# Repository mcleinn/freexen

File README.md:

Building blocks for a DIY 56*x key velocity-sensitive microtonal keyboard

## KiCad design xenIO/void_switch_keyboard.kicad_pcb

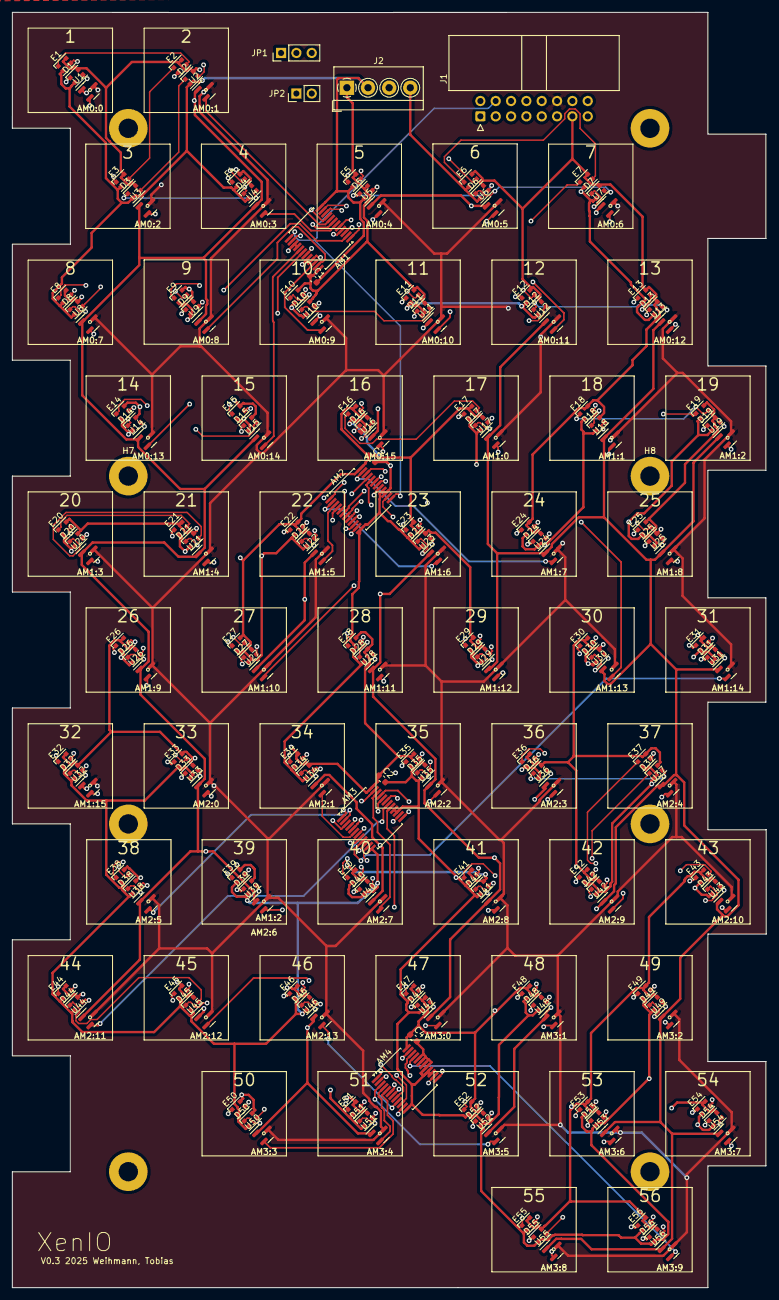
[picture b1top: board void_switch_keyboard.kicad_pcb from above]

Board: 4 copper layers, 124.8 x 211.2 mm, 244 parts (0 on the bottom side), 183 nets.

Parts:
AM0:0: 1; VoidSwitch_1u_SMD
AM0:1: 2; VoidSwitch_1u_SMD
AM0:2: 3; VoidSwitch_1u_SMD
AM0:3: 4; VoidSwitch_1u_SMD
AM0:4: 5; VoidSwitch_1u_SMD
AM0:5: 6; VoidSwitch_1u_SMD
AM0:6: 7; VoidSwitch_1u_SMD
AM0:7: 8; VoidSwitch_1u_SMD
AM0:8: 9; VoidSwitch_1u_SMD
AM0:9: 10; VoidSwitch_1u_SMD
AM0:10: 11; VoidSwitch_1u_SMD
AM0:11: 12; VoidSwitch_1u_SMD
AM0:12: 13; VoidSwitch_1u_SMD
AM0:13: 14; VoidSwitch_1u_SMD
AM0:14: 15; VoidSwitch_1u_SMD
AM0:15: 16; VoidSwitch_1u_SMD
AM1, AM2, AM3, AM4: CD74HC4067SM; SSOP-24_5.3x8.2mm_P0.65mm
AM1:0: 17; VoidSwitch_1u_SMD
AM1:1: 18; VoidSwitch_1u_SMD
AM1:2: 19; VoidSwitch_1u_SMD
AM1:3: 20; VoidSwitch_1u_SMD
AM1:4: 21; VoidSwitch_1u_SMD
AM1:5: 22; VoidSwitch_1u_SMD
AM1:6: 23; VoidSwitch_1u_SMD
AM1:7: 24; VoidSwitch_1u_SMD
AM1:8: 25; VoidSwitch_1u_SMD
AM1:9: 26; VoidSwitch_1u_SMD
AM1:10: 27; VoidSwitch_1u_SMD
AM1:11: 28; VoidSwitch_1u_SMD
AM1:12: 29; VoidSwitch_1u_SMD
AM1:13: 30; VoidSwitch_1u_SMD
AM1:14: 31; VoidSwitch_1u_SMD
AM1:15: 32; VoidSwitch_1u_SMD
AM2:0: 33; VoidSwitch_1u_SMD
AM2:1: 34; VoidSwitch_1u_SMD
AM2:2: 35; VoidSwitch_1u_SMD
AM2:3: 36; VoidSwitch_1u_SMD
AM2:4: 37; VoidSwitch_1u_SMD
AM2:5: 38; VoidSwitch_1u_SMD
AM2:6: 39; VoidSwitch_1u_SMD
AM2:7: 40; VoidSwitch_1u_SMD
AM2:8: 41; VoidSwitch_1u_SMD
AM2:9: 42; VoidSwitch_1u_SMD
AM2:10: 43; VoidSwitch_1u_SMD
AM2:11: 44; VoidSwitch_1u_SMD
AM2:12: 45; VoidSwitch_1u_SMD
AM2:13: 46; VoidSwitch_1u_SMD
AM3:0: 47; VoidSwitch_1u_SMD
AM3:1: 48; VoidSwitch_1u_SMD
AM3:2: 49; VoidSwitch_1u_SMD
AM3:3: 50; VoidSwitch_1u_SMD
AM3:4: 51; VoidSwitch_1u_SMD
AM3:5: 52; VoidSwitch_1u_SMD
AM3:6: 53; VoidSwitch_1u_SMD
AM3:7: 54; VoidSwitch_1u_SMD
AM3:8: 55; VoidSwitch_1u_SMD
AM3:9: 56; VoidSwitch_1u_SMD
C1, C2, C3, C4: 0.1uF; C_0603_1608Metric
D1, D2, D3, D4, D5, D6, D7, D8, D9, D10, D11, D12, D13, D14, D15, D16, D17, D18, D19, D20, D21, D22, D23, D24, D25, D26, D27, D28, D29, D30, D31, D32, D33, D34, D35, D36, D37, D38, D39, D40, D41, D42, D43, D44, D45, D46, D47, D48, D49, D50, D51, D52, D53, D54, D55, D56: WS2812B-2020; LED_WS2812B-2020_PLCC4_2.0x2.0mm
E1, E2, E3, E4, E5, E6, E7, E8, E9, E10, E11, E12, E13, E14, E15, E16, E17, E18, E19, E20, E21, E22, E23, E24, E25, E26, E27, E28, E29, E30, E31, E32, E33, E34, E35, E36, E37, E38, E39, E40, E41, E42, E43, E44, E45, E46, E47, E48, E49, E50, E51, E52, E53, E54, E55, E56: WS2812B-2020; LED_WS2812B-2020_PLCC4_2.0x2.0mm
H1, H2, H3, H4, H5, H6, H7, H8: MountingHole; MountingHole_3.2mm_M3_Pad
J1: CONTROLLER; IDC-Header_2x08_P2.54mm_Horizontal
J2: PWR; TerminalBlock_4Ucon_1x04_P3.50mm_Horizontal
JP1: JMP_LED1; PinHeader_1x03_P2.54mm_Vertical
JP2: JMP_LED2; PinHeader_1x02_P2.54mm_Vertical
U1, U2, U3, U4, U5, U6, U7, U8, U9, U10, U11, U12, U13, U14, U15, U16, U17, U18, U19, U20, U21, U22, U23, U24, U25, U26, U27, U28, U29, U30, U31, U32, U33, U34, U35, U36, U37, U38, U39, U40, U41, U42, U43, U44, U45, U46, U47, U48, U49, U50, U51, U52, U53, U54, U55, U56: GH39FKSW; SOT-23

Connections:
AM0: AM1.1 (COM), J1.5
AM0:0: AM1.9 (I0), U1.2 (OUT)
AM0:1: AM1.8 (I1), U2.2 (OUT)
AM0:2: AM1.7 (I2), U3.2 (OUT)
AM0:3: AM1.6 (I3), U4.2 (OUT)
AM0:4: AM1.5 (I4), U5.2 (OUT)
AM0:5: AM1.4 (I5), U6.2 (OUT)
AM0:6: AM1.3 (I6), U7.2 (OUT)
AM0:7: AM1.2 (I7), U8.2 (OUT)
AM0:8: AM1.23 (I8), U9.2 (OUT)
AM0:9: AM1.22 (I9), U10.2 (OUT)
AM0:10: AM1.21 (I10), U11.2 (OUT)
AM0:11: AM1.20 (I11), U12.2 (OUT)
AM0:12: AM1.19 (I12), U13.2 (OUT)
AM0:13: AM1.18 (I13), U14.2 (OUT)
AM0:14: AM1.17 (I14), U15.2 (OUT)
AM0:15: AM2.9 (I0), U16.2 (OUT)
AM1: AM2.1 (COM), J1.6
AM1:0: AM2.8 (I1), U17.2 (OUT)
AM1:1: AM2.7 (I2), U18.2 (OUT)
AM1:2: AM2.6 (I3), U19.2 (OUT)
AM1:3: AM2.5 (I4), U20.2 (OUT)
AM1:4: AM2.4 (I5), U21.2 (OUT)
AM1:5: AM2.3 (I6), U22.2 (OUT)
AM1:6: AM2.2 (I7), U23.2 (OUT)
AM1:7: AM2.23 (I8), U24.2 (OUT)
AM1:8: AM2.22 (I9), U25.2 (OUT)
AM1:9: AM2.21 (I10), U26.2 (OUT)
AM1:10: AM2.20 (I11), U27.2 (OUT)
AM1:11: AM2.19 (I12), U28.2 (OUT)
AM1:12: AM2.18 (I13), U29.2 (OUT)
AM1:13: AM2.17 (I14), U30.2 (OUT)
AM1:14: AM3.9 (I0), U31.2 (OUT)
AM1:15: AM3.8 (I1), U32.2 (OUT)
AM2: AM3.1 (COM), J1.7
AM2:0: AM3.7 (I2), U33.2 (OUT)
AM2:1: AM3.6 (I3), U34.2 (OUT)
AM2:2: AM3.5 (I4), U35.2 (OUT)
AM2:3: AM3.4 (I5), U36.2 (OUT)
AM2:4: AM3.3 (I6), U37.2 (OUT)
AM2:5: AM3.2 (I7), U38.2 (OUT)
AM2:6: AM3.23 (I8), U39.2 (OUT)
AM2:7: AM3.22 (I9), U40.2 (OUT)
AM2:8: AM3.21 (I10), U41.2 (OUT)
AM2:9: AM3.20 (I11), U42.2 (OUT)
AM2:10: AM3.19 (I12), U43.2 (OUT)
AM2:11: AM3.18 (I13), U44.2 (OUT)
AM2:12: AM3.17 (I14), U45.2 (OUT)
AM2:13: AM4.9 (I0), U46.2 (OUT)
AM3: AM4.1 (COM), J1.8
AM3:0: AM4.8 (I1), U47.2 (OUT)
AM3:1: AM4.7 (I2), U48.2 (OUT)
AM3:2: AM4.6 (I3), U49.2 (OUT)
AM3:3: AM4.5 (I4), U50.2 (OUT)
AM3:4: AM4.4 (I5), U51.2 (OUT)
AM3:5: AM4.3 (I6), U52.2 (OUT)
AM3:6: AM4.2 (I7), U53.2 (OUT)
AM3:7: AM4.23 (I8), U54.2 (OUT)
AM3:8: AM4.22 (I9), U55.2 (OUT)
AM3:9: AM4.21 (I10), U56.2 (OUT)
GNDLED: AM1.12 (GND), AM1.15 (~E), AM1.16 (I15), AM2.12 (GND), AM2.15 (~E), AM2.16 (I15), AM3.12 (GND), AM3.15 (~E), AM3.16 (I15), AM4.12 (GND), AM4.15 (~E), AM4.16 (I15), AM4.17 (I14), AM4.18 (I13), AM4.19 (I12), AM4.20 (I11), C1.2, C2.2, C3.2, C4.2, D1.2 (VSS), D2.2 (VSS), D3.2 (VSS), D4.2 (VSS), D5.2 (VSS), D6.2 (VSS), D7.2 (VSS), D8.2 (VSS), D9.2 (VSS), D10.2 (VSS), D11.2 (VSS), D12.2 (VSS), D13.2 (VSS), D14.2 (VSS), D15.2 (VSS), D16.2 (VSS), D17.2 (VSS), D18.2 (VSS), D19.2 (VSS), D20.2 (VSS), D21.2 (VSS), D22.2 (VSS), D23.2 (VSS), D24.2 (VSS), D25.2 (VSS), D26.2 (VSS), D27.2 (VSS), D28.2 (VSS), D29.2 (VSS), D30.2 (VSS), D31.2 (VSS), D32.2 (VSS), D33.2 (VSS), D34.2 (VSS), D35.2 (VSS), D36.2 (VSS), D37.2 (VSS), D38.2 (VSS), D39.2 (VSS), D40.2 (VSS), D41.2 (VSS), D42.2 (VSS), D43.2 (VSS), D44.2 (VSS), D45.2 (VSS), D46.2 (VSS), D47.2 (VSS), D48.2 (VSS), D49.2 (VSS), D50.2 (VSS), D51.2 (VSS), D52.2 (VSS), D53.2 (VSS), D54.2 (VSS), D55.2 (VSS), D56.2 (VSS), E1.2 (VSS), E2.2 (VSS), E3.2 (VSS), E4.2 (VSS), E5.2 (VSS), E6.2 (VSS), E7.2 (VSS), E8.2 (VSS), E9.2 (VSS), E10.2 (VSS), E11.2 (VSS), E12.2 (VSS), E13.2 (VSS), E14.2 (VSS), E15.2 (VSS), E16.2 (VSS), E17.2 (VSS), E18.2 (VSS), E19.2 (VSS), E20.2 (VSS), E21.2 (VSS), E22.2 (VSS), E23.2 (VSS), E24.2 (VSS), E25.2 (VSS), E26.2 (VSS), E27.2 (VSS), E28.2 (VSS), E29.2 (VSS), E30.2 (VSS), E31.2 (VSS), E32.2 (VSS), E33.2 (VSS), E34.2 (VSS), E35.2 (VSS), E36.2 (VSS), E37.2 (VSS), E38.2 (VSS), E39.2 (VSS), E40.2 (VSS), E41.2 (VSS), E42.2 (VSS), E43.2 (VSS), E44.2 (VSS), E45.2 (VSS), E46.2 (VSS), E47.2 (VSS), E48.2 (VSS), E49.2 (VSS), E50.2 (VSS), E51.2 (VSS), E52.2 (VSS), E53.2 (VSS), E54.2 (VSS), E55.2 (VSS), E56.2 (VSS), J1.15, J1.16, J2.2, J2.4
GNDSENSOR: J1.12, U1.3 (GND), U2.3 (GND), U3.3 (GND), U4.3 (GND), U5.3 (GND), U6.3 (GND), U7.3 (GND), U8.3 (GND), U9.3 (GND), U10.3 (GND), U11.3 (GND), U12.3 (GND), U13.3 (GND), U14.3 (GND), U15.3 (GND), U16.3 (GND), U17.3 (GND), U18.3 (GND), U19.3 (GND), U20.3 (GND), U21.3 (GND), U22.3 (GND), U23.3 (GND), U24.3 (GND), U25.3 (GND), U26.3 (GND), U27.3 (GND), U28.3 (GND), U29.3 (GND), U30.3 (GND), U31.3 (GND), U32.3 (GND), U33.3 (GND), U34.3 (GND), U35.3 (GND), U36.3 (GND), U37.3 (GND), U38.3 (GND), U39.3 (GND), U40.3 (GND), U41.3 (GND), U42.3 (GND), U43.3 (GND), U44.3 (GND), U45.3 (GND), U46.3 (GND), U47.3 (GND), U48.3 (GND), U49.3 (GND), U50.3 (GND), U51.3 (GND), U52.3 (GND), U53.3 (GND), U54.3 (GND), U55.3 (GND), U56.3 (GND)
LDIN: D1.3 (DIN), J1.9
LDIN2: E1.3 (DIN), JP1.1 (A)
LDOUT: J1.10, JP1.3 (B), JP2.2 (B)
LDOUT1: D56.1 (DOUT), JP1.2 (C)
LDOUT2: E56.1 (DOUT), JP2.1 (A)
unnamed: D1.1 (DOUT), D2.3 (DIN)
unnamed: D2.1 (DOUT), D3.3 (DIN)
unnamed: D3.1 (DOUT), D4.3 (DIN)
unnamed: D4.1 (DOUT), D5.3 (DIN)
unnamed: D5.1 (DOUT), D6.3 (DIN)
unnamed: D6.1 (DOUT), D7.3 (DIN)
unnamed: D7.1 (DOUT), D8.3 (DIN)
unnamed: D8.1 (DOUT), D9.3 (DIN)
unnamed: D9.1 (DOUT), D10.3 (DIN)
unnamed: D10.1 (DOUT), D11.3 (DIN)
unnamed: D11.1 (DOUT), D12.3 (DIN)
unnamed: D12.1 (DOUT), D13.3 (DIN)
unnamed: D13.1 (DOUT), D14.3 (DIN)
unnamed: D14.1 (DOUT), D15.3 (DIN)
unnamed: D15.1 (DOUT), D16.3 (DIN)
unnamed: D16.1 (DOUT), D17.3 (DIN)
unnamed: D17.1 (DOUT), D18.3 (DIN)
unnamed: D18.1 (DOUT), D19.3 (DIN)
unnamed: D19.1 (DOUT), D20.3 (DIN)
unnamed: D20.1 (DOUT), D21.3 (DIN)
unnamed: D21.1 (DOUT), D22.3 (DIN)
unnamed: D22.1 (DOUT), D23.3 (DIN)
unnamed: D23.1 (DOUT), D24.3 (DIN)
unnamed: D24.1 (DOUT), D25.3 (DIN)
unnamed: D25.1 (DOUT), D26.3 (DIN)
unnamed: D26.1 (DOUT), D27.3 (DIN)
unnamed: D27.1 (DOUT), D28.3 (DIN)
unnamed: D28.1 (DOUT), D29.3 (DIN)
unnamed: D29.1 (DOUT), D30.3 (DIN)
unnamed: D30.1 (DOUT), D31.3 (DIN)
unnamed: D31.1 (DOUT), D32.3 (DIN)
unnamed: D32.1 (DOUT), D33.3 (DIN)
unnamed: D33.1 (DOUT), D34.3 (DIN)
unnamed: D34.1 (DOUT), D35.3 (DIN)
unnamed: D35.1 (DOUT), D36.3 (DIN)
unnamed: D36.1 (DOUT), D37.3 (DIN)
unnamed: D37.1 (DOUT), D38.3 (DIN)
unnamed: D38.1 (DOUT), D39.3 (DIN)
unnamed: D39.1 (DOUT), D40.3 (DIN)
unnamed: D40.1 (DOUT), D41.3 (DIN)
unnamed: D41.1 (DOUT), D42.3 (DIN)
unnamed: D42.1 (DOUT), D43.3 (DIN)
unnamed: D43.1 (DOUT), D44.3 (DIN)
unnamed: D44.1 (DOUT), D45.3 (DIN)
unnamed: D45.1 (DOUT), D46.3 (DIN)
unnamed: D46.1 (DOUT), D47.3 (DIN)
unnamed: D47.1 (DOUT), D48.3 (DIN)
unnamed: D48.1 (DOUT), D49.3 (DIN)
unnamed: D49.1 (DOUT), D50.3 (DIN)
unnamed: D50.1 (DOUT), D51.3 (DIN)
unnamed: D51.1 (DOUT), D52.3 (DIN)
unnamed: D52.1 (DOUT), D53.3 (DIN)
unnamed: D53.1 (DOUT), D54.3 (DIN)
unnamed: D54.1 (DOUT), D55.3 (DIN)
unnamed: D55.1 (DOUT), D56.3 (DIN)
unnamed: E1.1 (DOUT), E2.3 (DIN)
unnamed: E2.1 (DOUT), E3.3 (DIN)
unnamed: E3.1 (DOUT), E4.3 (DIN)
unnamed: E4.1 (DOUT), E5.3 (DIN)
unnamed: E5.1 (DOUT), E6.3 (DIN)
unnamed: E6.1 (DOUT), E7.3 (DIN)
unnamed: E7.1 (DOUT), E8.3 (DIN)
unnamed: E8.1 (DOUT), E9.3 (DIN)
unnamed: E9.1 (DOUT), E10.3 (DIN)
unnamed: E10.1 (DOUT), E11.3 (DIN)
unnamed: E11.1 (DOUT), E12.3 (DIN)
unnamed: E12.1 (DOUT), E13.3 (DIN)
unnamed: E13.1 (DOUT), E14.3 (DIN)
unnamed: E14.1 (DOUT), E15.3 (DIN)
unnamed: E15.1 (DOUT), E16.3 (DIN)
unnamed: E16.1 (DOUT), E17.3 (DIN)
unnamed: E17.1 (DOUT), E18.3 (DIN)
unnamed: E18.1 (DOUT), E19.3 (DIN)
unnamed: E19.1 (DOUT), E20.3 (DIN)
unnamed: E20.1 (DOUT), E21.3 (DIN)
unnamed: E21.1 (DOUT), E22.3 (DIN)
unnamed: E22.1 (DOUT), E23.3 (DIN)
unnamed: E23.1 (DOUT), E24.3 (DIN)
unnamed: E24.1 (DOUT), E25.3 (DIN)
unnamed: E25.1 (DOUT), E26.3 (DIN)
unnamed: E26.1 (DOUT), E27.3 (DIN)
unnamed: E27.1 (DOUT), E28.3 (DIN)
unnamed: E28.1 (DOUT), E29.3 (DIN)
unnamed: E29.1 (DOUT), E30.3 (DIN)
unnamed: E30.1 (DOUT), E31.3 (DIN)
unnamed: E31.1 (DOUT), E32.3 (DIN)
unnamed: E32.1 (DOUT), E33.3 (DIN)
unnamed: E33.1 (DOUT), E34.3 (DIN)
unnamed: E34.1 (DOUT), E35.3 (DIN)
unnamed: E35.1 (DOUT), E36.3 (DIN)
unnamed: E36.1 (DOUT), E37.3 (DIN)
unnamed: E37.1 (DOUT), E38.3 (DIN)
unnamed: E38.1 (DOUT), E39.3 (DIN)
unnamed: E39.1 (DOUT), E40.3 (DIN)
unnamed: E40.1 (DOUT), E41.3 (DIN)
unnamed: E41.1 (DOUT), E42.3 (DIN)
unnamed: E42.1 (DOUT), E43.3 (DIN)
unnamed: E43.1 (DOUT), E44.3 (DIN)
unnamed: E44.1 (DOUT), E45.3 (DIN)
unnamed: E45.1 (DOUT), E46.3 (DIN)
unnamed: E46.1 (DOUT), E47.3 (DIN)
unnamed: E47.1 (DOUT), E48.3 (DIN)
unnamed: E48.1 (DOUT), E49.3 (DIN)
unnamed: E49.1 (DOUT), E50.3 (DIN)
unnamed: E50.1 (DOUT), E51.3 (DIN)
unnamed: E51.1 (DOUT), E52.3 (DIN)
unnamed: E52.1 (DOUT), E53.3 (DIN)
unnamed: E53.1 (DOUT), E54.3 (DIN)
unnamed: E54.1 (DOUT), E55.3 (DIN)
unnamed: E55.1 (DOUT), E56.3 (DIN)
SELECT0: AM1.10 (S0), AM2.10 (S0), AM3.10 (S0), AM4.10 (S0), J1.1
SELECT1: AM1.11 (S1), AM2.11 (S1), AM3.11 (S1), AM4.11 (S1), J1.2
SELECT2: AM1.14 (S2), AM2.14 (S2), AM3.14 (S2), AM4.14 (S2), J1.3
SELECT3: AM1.13 (S3), AM2.13 (S3), AM3.13 (S3), AM4.13 (S3), J1.4
VLED: AM1.24 (VCC), AM2.24 (VCC), AM3.24 (VCC), AM4.24 (VCC), C1.1, C2.1, C3.1, C4.1, D1.4 (VDD), D2.4 (VDD), D3.4 (VDD), D4.4 (VDD), D5.4 (VDD), D6.4 (VDD), D7.4 (VDD), D8.4 (VDD), D9.4 (VDD), D10.4 (VDD), D11.4 (VDD), D12.4 (VDD), D13.4 (VDD), D14.4 (VDD), D15.4 (VDD), D16.4 (VDD), D17.4 (VDD), D18.4 (VDD), D19.4 (VDD), D20.4 (VDD), D21.4 (VDD), D22.4 (VDD), D23.4 (VDD), D24.4 (VDD), D25.4 (VDD), D26.4 (VDD), D27.4 (VDD), D28.4 (VDD), D29.4 (VDD), D30.4 (VDD), D31.4 (VDD), D32.4 (VDD), D33.4 (VDD), D34.4 (VDD), D35.4 (VDD), D36.4 (VDD), D37.4 (VDD), D38.4 (VDD), D39.4 (VDD), D40.4 (VDD), D41.4 (VDD), D42.4 (VDD), D43.4 (VDD), D44.4 (VDD), D45.4 (VDD), D46.4 (VDD), D47.4 (VDD), D48.4 (VDD), D49.4 (VDD), D50.4 (VDD), D51.4 (VDD), D52.4 (VDD), D53.4 (VDD), D54.4 (VDD), D55.4 (VDD), D56.4 (VDD), E1.4 (VDD), E2.4 (VDD), E3.4 (VDD), E4.4 (VDD), E5.4 (VDD), E6.4 (VDD), E7.4 (VDD), E8.4 (VDD), E9.4 (VDD), E10.4 (VDD), E11.4 (VDD), E12.4 (VDD), E13.4 (VDD), E14.4 (VDD), E15.4 (VDD), E16.4 (VDD), E17.4 (VDD), E18.4 (VDD), E19.4 (VDD), E20.4 (VDD), E21.4 (VDD), E22.4 (VDD), E23.4 (VDD), E24.4 (VDD), E25.4 (VDD), E26.4 (VDD), E27.4 (VDD), E28.4 (VDD), E29.4 (VDD), E30.4 (VDD), E31.4 (VDD), E32.4 (VDD), E33.4 (VDD), E34.4 (VDD), E35.4 (VDD), E36.4 (VDD), E37.4 (VDD), E38.4 (VDD), E39.4 (VDD), E40.4 (VDD), E41.4 (VDD), E42.4 (VDD), E43.4 (VDD), E44.4 (VDD), E45.4 (VDD), E46.4 (VDD), E47.4 (VDD), E48.4 (VDD), E49.4 (VDD), E50.4 (VDD), E51.4 (VDD), E52.4 (VDD), E53.4 (VDD), E54.4 (VDD), E55.4 (VDD), E56.4 (VDD), J1.13, J1.14, J2.1, J2.3
VSENS: J1.11, U1.1 (VDD), U2.1 (VDD), U3.1 (VDD), U4.1 (VDD), U5.1 (VDD), U6.1 (VDD), U7.1 (VDD), U8.1 (VDD), U9.1 (VDD), U10.1 (VDD), U11.1 (VDD), U12.1 (VDD), U13.1 (VDD), U14.1 (VDD), U15.1 (VDD), U16.1 (VDD), U17.1 (VDD), U18.1 (VDD), U19.1 (VDD), U20.1 (VDD), U21.1 (VDD), U22.1 (VDD), U23.1 (VDD), U24.1 (VDD), U25.1 (VDD), U26.1 (VDD), U27.1 (VDD), U28.1 (VDD), U29.1 (VDD), U30.1 (VDD), U31.1 (VDD), U32.1 (VDD), U33.1 (VDD), U34.1 (VDD), U35.1 (VDD), U36.1 (VDD), U37.1 (VDD), U38.1 (VDD), U39.1 (VDD), U40.1 (VDD), U41.1 (VDD), U42.1 (VDD), U43.1 (VDD), U44.1 (VDD), U45.1 (VDD), U46.1 (VDD), U47.1 (VDD), U48.1 (VDD), U49.1 (VDD), U50.1 (VDD), U51.1 (VDD), U52.1 (VDD), U53.1 (VDD), U54.1 (VDD), U55.1 (VDD), U56.1 (VDD)

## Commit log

2025-02-24 Initial upload
2025-02-24 Add submodules
2025-02-24 Adding 3D printing plates
2025-02-27 Fixed bugs in XenAssist
2025-02-27 Fix issues before presentation
2025-02-27 Update xenKeycap submodule pointer to latest commit
2025-02-27 Update xenSwitch submodule pointer to the latest commit
2025-02-27 Fixed issues in programmer (color encoding)
2025-03-01 Last update before presentation
2025-03-23 Add VisualStudioCode project
2025-05-10 Improve development/debugging system
2026-02-21 Checkpoint current calibration and debug changes
2026-02-22 Fix calibration persistence and diagnostics
2026-02-22 Add calibration issue persistence and meta dump
2026-02-22 Update MCP config and remove duplicate
2026-02-22 Fix autotune best selection and add idle120 validation
2026-02-23 Reapply post-68 firmware fixes
2026-02-23 Add boot drift compensation and commands
2026-02-23 Restore calibration slot backup/restore commands
2026-02-23 Add autotune overlay persistence and progress output
2026-02-23 Start autotune at stable avg/sd defaults
2026-02-23 Add JSONL output for calib slot commands
2026-02-23 Echo ack command string in OK line
2026-02-23 Echo OK with command and update MCP config
2026-02-23 Include command description in OK ack
2026-02-23 Adjust OK ack formatting
2026-02-23 Remove autotune maxThr clamp
2026-02-23 Guarantee strict autotune reaches zero and flag dynamics
2026-02-23 Pause normal scanning on debug attach
2026-02-23 Use effective thresholds for MIDI peak detection
2026-02-23 Add scan rate and dynamics step metrics; add baseline drift tracker
2026-02-23 Add noiselevel/noisereset commands and metrics
2026-02-23 Add noise and calibration tools guide
2026-02-23 Document calibration, baseline drift, and autotune layers
2026-02-23 Add xenctl serial supervisor script
2026-02-23 Add autotune_done marker and speed up autotune defaults
2026-02-23 Bump fw to 91; add JSONL peak debug; improve xenctl + docs
